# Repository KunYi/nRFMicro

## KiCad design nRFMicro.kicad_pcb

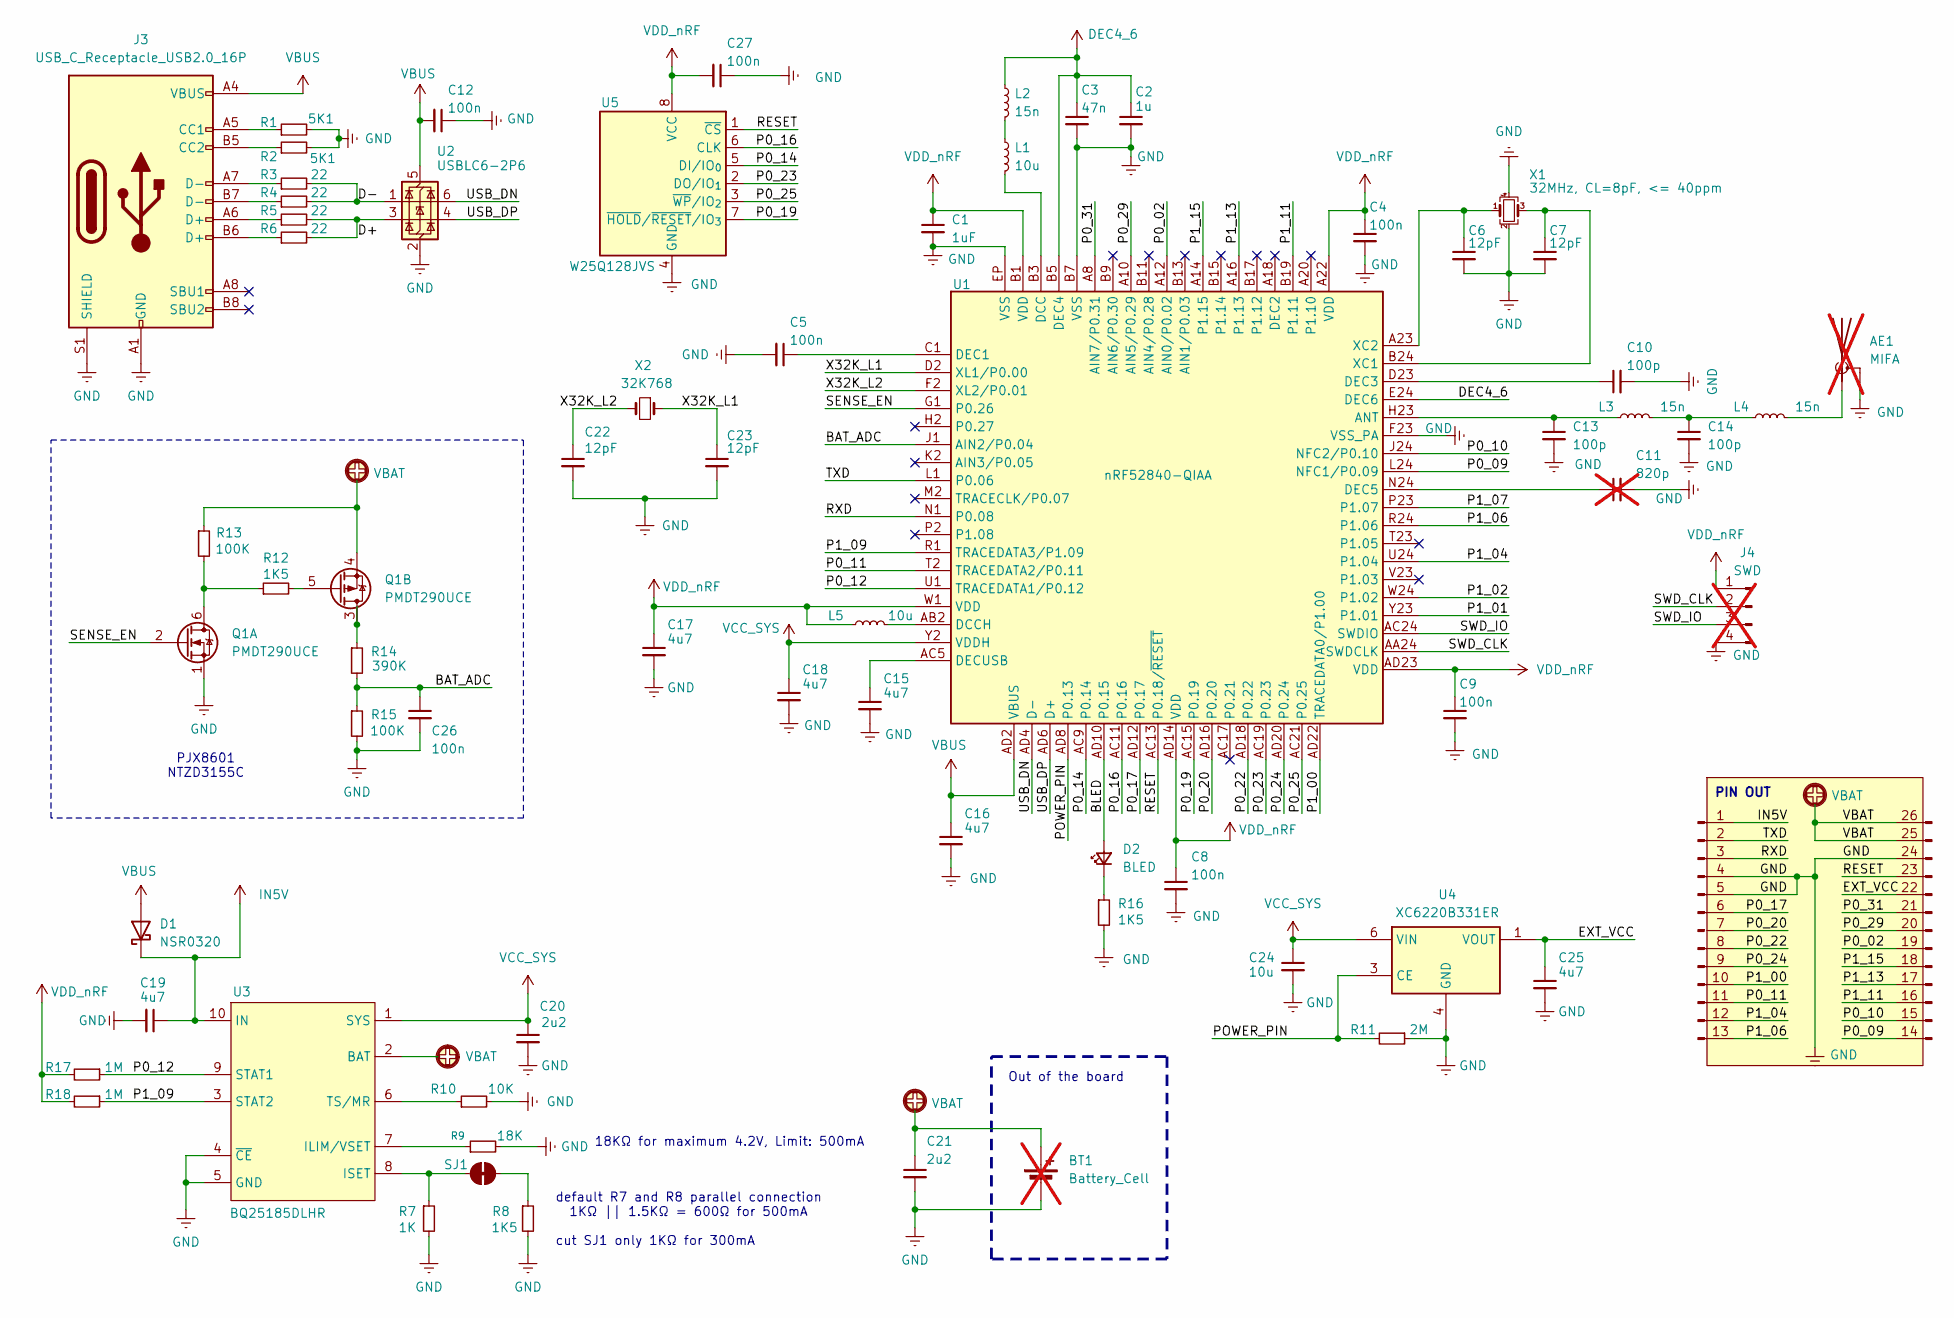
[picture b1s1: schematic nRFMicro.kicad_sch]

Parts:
AE1: MIFA; BLE_ANTENNA; not fitted
BP1: ProMicroPinHeader
BT1: Battery_Cell; not fitted
C1: 1uF; C_0402_1005Metric; Part No GRM155Z71A105KE1D; LCSC C528974
C2: 1u; C_0402_1005Metric; Part No GRM155Z71A105KE1D; LCSC C528974
C3: 47n; C_0402_1005Metric; Part No GRM155Z71A105KE1D; LCSC C528974
C4, C5, C8, C9, C12, C26, C27: 100n; C_0402_1005Metric; Part No GRM155Z71A105KE1D; LCSC C528974
C6, C7, C22, C23: 12pF; C_0402_1005Metric; Part No GRM155Z71A105KE1D; LCSC C528974
C10, C13, C14: 100p; C_0402_1005Metric; Part No GRM155Z71A105KE1D; LCSC C528974
C11: 820p; C_0402_1005Metric; Part No GRM155Z71A105KE1D; LCSC C528974; not fitted
C15, C16, C17, C18, C19, C25: 4u7; C_0402_1005Metric; Part No CL05A475MO5NUNC; LCSC C318563
C20, C21: 2u2; C_0402_1005Metric; Part No GRM155Z71A105KE1D; LCSC C528974
C24: 10u; C_0402_1005Metric; Part No CL05A475MO5NUNC; LCSC C318563
D1: NSR0320; D_SOD-323; Part No NSR0320MW2T1G; LCSC C48192
D2: BLED; LED_0402_1005Metric
J3: USB_C_Receptacle_USB2.0_16P; USB-C_C168688; Part No 918-418K2024S40000; LCSC C168688
J4: SWD; SWD_CONNECTOR; not fitted
L1, L5: 10u; L_0603_1608Metric; Part No MLZ1608E100MT; LCSC C340673
L2, L3, L4: 15n; L_0402_1005Metric; Part No MLZ1608E100MT; LCSC C340673
Q1: PMDT290UCE; SOT-666
R1, R2: 5K1; R_0402_1005Metric
R3, R4, R5, R6: 22; R_0402_1005Metric
R7: 1K; R_0402_1005Metric
R8, R12, R16: 1K5; R_0402_1005Metric
R9: 18K; R_0402_1005Metric
R10: 10K; StrappingJumpR
R11: 2M; R_0402_1005Metric
R13, R15: 100K; R_0402_1005Metric
R14: 390K; R_0402_1005Metric
R17, R18: 1M; R_0402_1005Metric
SJ1: StrappingJump
U1: nRF52840-QIAA; Nordic_AQFN-73-1EP_7x7mm_P0.5mm
U2: USBLC6-2P6; LCSC C2827693
U3: BQ25185DLHR; Part No BQ25185DLHR; LCSC C19725033
U4: XC6220B331ER; USP6-C
U5: W25Q128JVS; SOIC-8_5.3x5.3mm_P1.27mm
X1: 32MHz, CL=8pF, <= 40ppm; Crystal_SMD_SeikoEpson_FA128-4Pin_2.0x1.6mm
X2: 32K768; SMD2016-2P; Part No SC20S-12.5PF20PPM; LCSC C97607

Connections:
/BAT_ADC: C26.1, R14.2, R15.1, U1.J1 (AIN2/P0.04)
/BLED: D2.2 (A), U1.AD10 (P0.15)
/D+: R5.2, R6.2, U2.3 (I/O2)
/D-: R3.2, R4.2, U2.1 (I/O1)
/P0_02: BP1.19, U1.A12 (AIN0/P0.02)
/P0_09: BP1.14, U1.L24 (NFC1/P0.09)
/P0_10: BP1.15, U1.J24 (NFC2/P0.10)
/P0_11: BP1.11, U1.T2 (TRACEDATA2/P0.11)
/P0_12: R17.1, U1.U1 (TRACEDATA1/P0.12), U3.9 (STAT1)
/P0_14: U1.AC9 (P0.14), U5.5 (DI/IO_{0})
/P0_16: U1.AC11 (P0.16), U5.6 (CLK)
/P0_17: BP1.6, U1.AD12 (P0.17)
/P0_19: U1.AC15 (P0.19), U5.7 (~HOLD/~RESET/IO_{3})
/P0_20: BP1.7, U1.AD16 (P0.20)
/P0_22: BP1.8, U1.AD18 (P0.22)
/P0_23: U1.AC19 (P0.23), U5.2 (DO/IO_{1})
/P0_24: BP1.9, U1.AD20 (P0.24)
/P0_25: U1.AC21 (P0.25), U5.3 (~WP/IO_{2})
/P0_29: BP1.20, U1.A10 (AIN5/P0.29)
/P0_31: BP1.21, U1.A8 (AIN7/P0.31)
/P1_00: BP1.10, U1.AD22 (TRACEDATA0/P1.00)
/P1_01: U1.Y23 (P1.01)
/P1_02: U1.W24 (P1.02)
/P1_04: BP1.12, U1.U24 (P1.04)
/P1_06: BP1.13, U1.R24 (P1.06)
/P1_07: U1.P23 (P1.07)
/P1_09: R18.1, U1.R1 (TRACEDATA3/P1.09), U3.3 (STAT2)
/P1_11: BP1.16, U1.B19 (P1.11)
/P1_13: BP1.17, U1.A16 (P1.13)
/P1_15: BP1.18, U1.A14 (P1.15)
/POWER_PIN: R11.2, U1.AD8 (P0.13), U4.3 (CE)
/RESET: BP1.23, U1.AC13 (P0.18/~RESET), U5.1 (~CS)
/RXD: BP1.3, U1.N1 (P0.08)
/SENSE_EN: Q1.2 (GN), U1.G1 (P0.26)
/SWD_CLK: J4.2, U1.AA24 (SWDCLK)
/SWD_IO: J4.3, U1.AC24 (SWDIO)
/TXD: BP1.2, U1.L1 (P0.06)
/USB_DN: U1.AD4 (D-), U2.6 (I/O1)
/USB_DP: U1.AD6 (D+), U2.4 (I/O2)
/X32K_L1: C23.1, U1.D2 (XL1/P0.00), X2.1
/X32K_L2: C22.1, U1.F2 (XL2/P0.01), X2.2
DEC4_6: C2.1, C3.1, L2.1, U1.B5 (DEC4), U1.E24 (DEC6)
GND: AE1.2 (Shield), BP1.4, BP1.5, BP1.24, BT1.2 (-), C1.2, C2.2, C3.2, C4.2, C5.2, C6.2, C7.2, C8.2, C9.2, C10.2, C11.2, C12.1, C13.2, C14.2, C15.2, C16.2, C17.2, C18.2, C19.2, C20.2, C21.2, C22.2, C23.2, C24.2, C25.2, C26.2, C27.1, J3.A1 (GND), J3.A12 (GND), J3.B1 (GND), J3.B12 (GND), J3.S1 (SHIELD), J3.S2 (SHIELD), J3.S3 (SHIELD), J3.S4 (SHIELD), J4.4, Q1.1 (SN), R1.2, R2.2, R7.2, R8.2, R9.2, R10.2, R11.1, R15.2, R16.2, U1.B7 (VSS), U1.EP (VSS), U1.F23 (VSS_PA), U2.2 (GND), U3.4 (~CE), U3.5 (GND), U3.11 (EP), U4.4 (GND), U4.EP, U5.4 (GND), X1.2, X1.4
IN5V: BP1.1, C19.1, D1.1 (K), U3.10 (IN)
unnamed: AE1.1 (A), L4.2
unnamed: C14.1, L3.2, L4.1
unnamed: D2.1 (K), R16.1
unnamed: J3.A5 (CC1), R1.1
unnamed: J3.B5 (CC2), R2.1
unnamed: J3.A6 (D+), R5.1
unnamed: J3.B6 (D+), R6.1
unnamed: J3.A7 (D-), R3.1
unnamed: J3.B7 (D-), R4.1
unnamed: L1.1, L2.2
unnamed: Q1.6 (DN), R12.1, R13.2
unnamed: Q1.3 (DP), R14.1
unnamed: Q1.5 (GP), R12.2
unnamed: R8.1, SJ1.2
unnamed: C13.1, L3.1, U1.H23 (ANT)
unnamed: L1.2, U1.B3 (DCC)
unnamed: L5.2, U1.AB2 (DCCH)
unnamed: C5.1, U1.C1 (DEC1)
unnamed: C10.1, U1.D23 (DEC3)
unnamed: C11.1, U1.N24 (DEC5)
unnamed: C15.1, U1.AC5 (DECUSB)
unnamed: C7.1, U1.B24 (XC1), X1.3
unnamed: C6.1, U1.A23 (XC2), X1.1
unnamed: R9.1, U3.7 (ILIM/VSET)
unnamed: R7.1, SJ1.1, U3.8 (ISET)
unnamed: R10.1, U3.6 (TS/MR)
VBAT: BP1.25, BP1.26, BT1.1 (+), C21.1, Q1.4 (SP), R13.1, U3.2 (BAT)
VBUS: C12.2, C16.1, D1.2 (A), J3.A4 (VBUS), J3.A9 (VBUS), J3.B4 (VBUS), J3.B9 (VBUS), U1.AD2 (VBUS), U2.5 (VBUS)
VCC_SYS: C18.1, C20.1, C24.1, U1.Y2 (VDDH), U3.1 (SYS), U4.5 (VIN), U4.6 (VIN)
VDD_nRF: C1.1, C4.1, C8.1, C9.1, C17.1, C27.2, J4.1, L5.1, R17.2, R18.2, U1.A22 (VDD), U1.AD14 (VDD), U1.AD23 (VDD), U1.B1 (VDD), U1.W1 (VDD), U5.8 (VCC)
VOUT: BP1.22, C25.1, U4.1 (VOUT), U4.2 (VOUT)

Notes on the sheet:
default R7 and R8 parallel connection 1KΩ || 1.5KΩ = 600Ω for 500mA cut SJ1 only 1KΩ for 300mA
PIN OUT
PJX8601 NTZD3155C
Out of the board
18KΩ for maximum 4.2V, Limit: 500mA

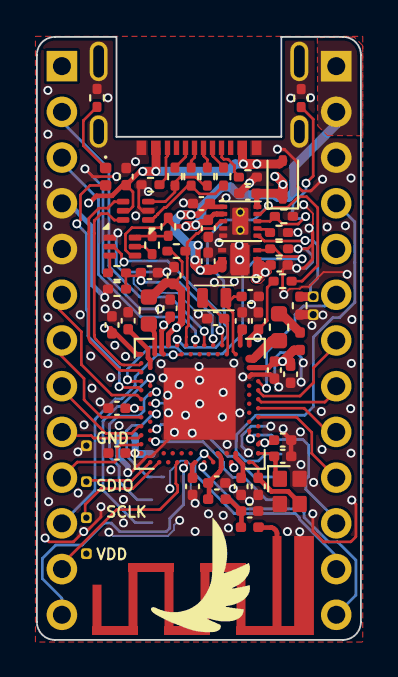
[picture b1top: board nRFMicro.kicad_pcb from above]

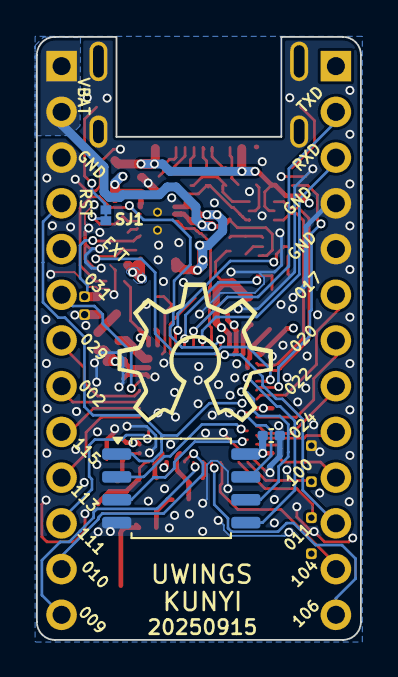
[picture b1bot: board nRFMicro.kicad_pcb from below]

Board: 4 copper layers, 18.0 x 33.5 mm, 65 parts (4 on the bottom side), 72 nets.

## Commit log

2025-09-06 initial version
2025-09-15 add Panelize version for 100mmx100mm
